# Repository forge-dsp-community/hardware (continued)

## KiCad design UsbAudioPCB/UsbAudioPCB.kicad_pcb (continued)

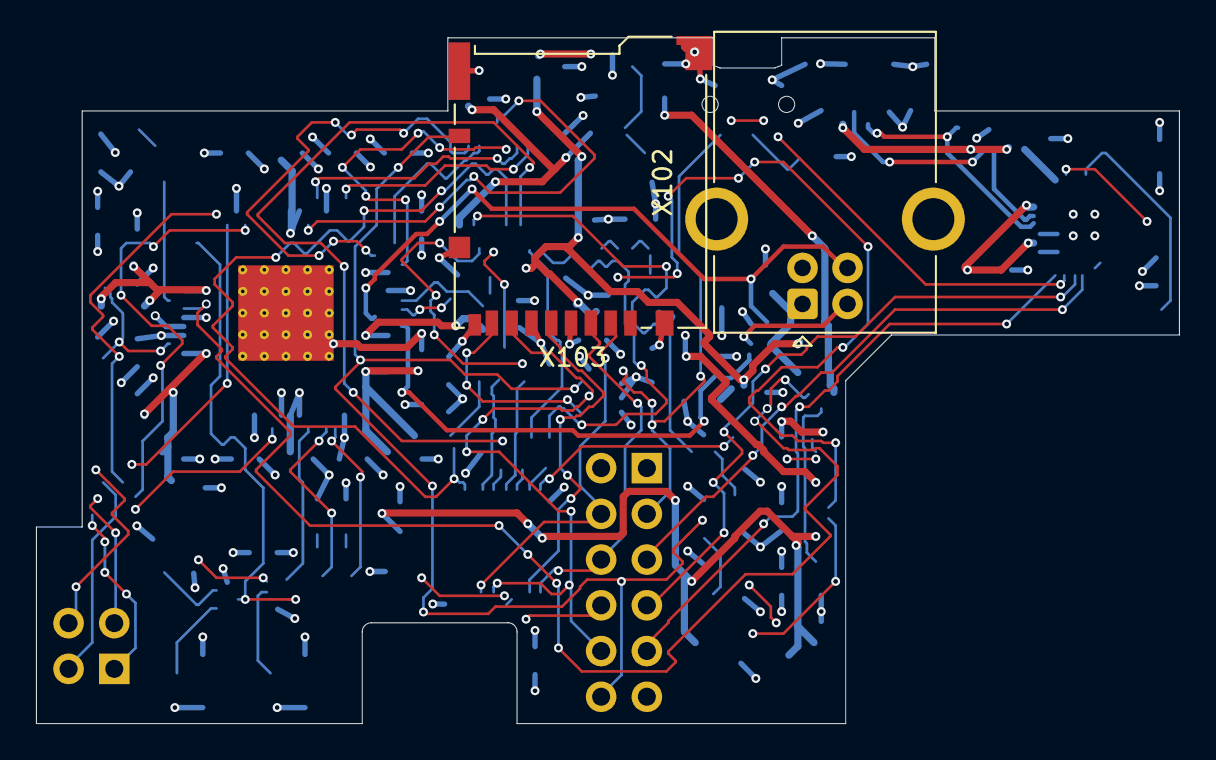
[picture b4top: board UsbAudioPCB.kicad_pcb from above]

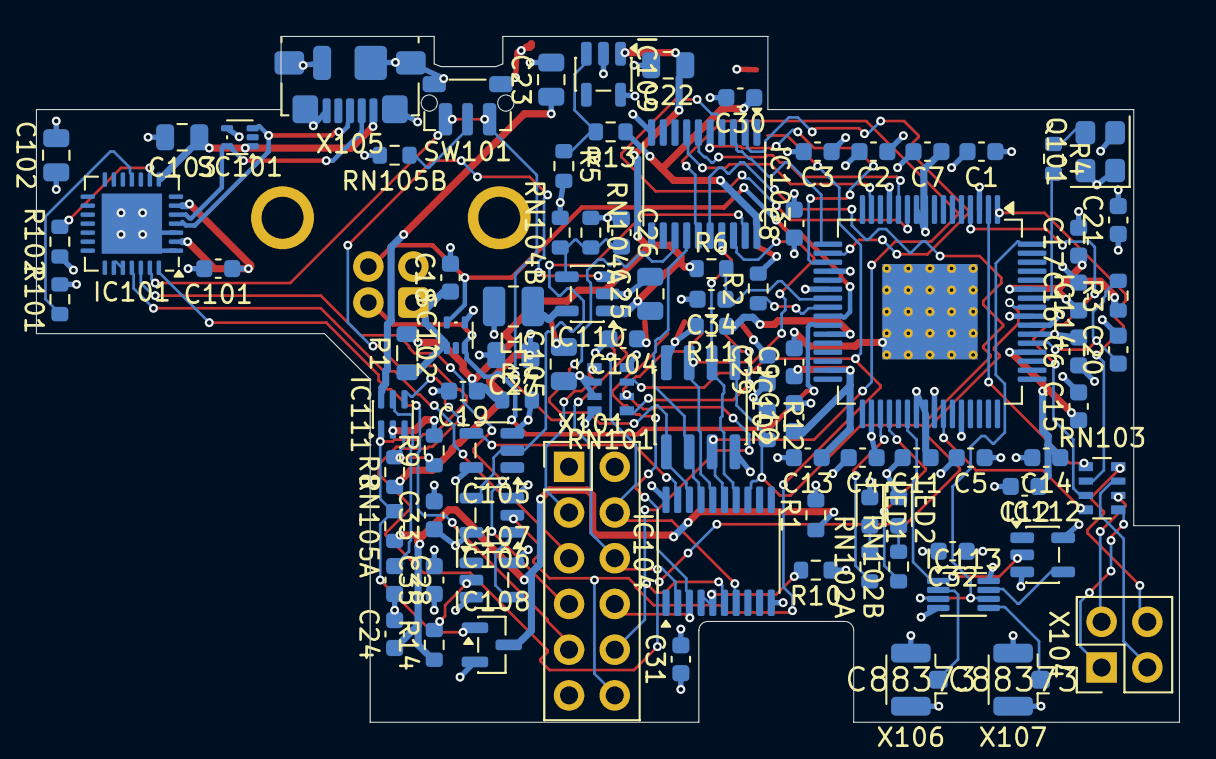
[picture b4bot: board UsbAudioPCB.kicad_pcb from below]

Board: 4 copper layers, 63.5 x 38.1 mm, 93 parts (91 on the bottom side), 71 nets.
